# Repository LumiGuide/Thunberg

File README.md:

# THUNBERG CLIMATE CONTROL

An infrared controller for Fuji and Mitsubishi climate control units.
Visit thunberg.lumi.guide and select the room of the climate control unit you want to control under 'Room:'. It will load the last settings that were sent to this unit using the website. Set the preferred temperature, mode, strenth and extra options under 'toppings'. Click 'Send' to send a signal with these settings to the climate control unit, or click 'Turn off' to turn the unit off.
At the bottom of the page, you can click 'KILL ALL' to turn off all units in the rooms listed under 'Room:'.
Every day between 19:00 and 19:15, all units will be turned off automatically.

## Troubleshooting
- No response from the climate control unit
The Thunberg device works with an IR-LED, make sure there is nothing blocking the IR signal from the Thunberg device to the climate control unit. Make sure the IR-LED is pointing directly at the climate control unit.

If the LED on the back of the device is green, the device is connected to the internet. If this is not the case, unplug the device and plug it in again to reboot. It should automatically connect to the internet.
If the wifi name and/or password has changed, you need to change this in the menuconfig and flash the device. (Open the menuconfig by navigating to the Thunberg folder and using the command `idf.py menuconfig` in your terminal. ESP-IDF should be installed and running for this.)

- The webpage keeps loading
If there's no room selected, the page will remain on the loading screen. As soon as you select a room, it will load the last settings that were sent to the climate control unit in this room.
If there's a room selected, but the page keeps showing the loading screen, the website doesn't get a response from the device you selected. Check the internet connection of the device.

- The webpage is offline
The Master Device is offline. Unplug the device and plug it in again to reboot. It should automatically reconnect to the internet.

- It's still not working
Connect the device to your computer using the USB programmer and plug in the charger. With ESP-IDF running, type `idf.py -p USB-PORT monitor` in your terminal to see the data log.

# HOW TO BUILD

## Parts
- M5Stack M5Stamp Pico, ESP32-PICO-D4 (https://www.tinytronics.nl/shop/en/platforms-and-systems/m5stack/m5stamp/m5stamp/m5stack-m5stamp-pico-mate-esp32-pico-d4)
- IR LED, super-bright, 5mm, 940nm (https://www.adafruit.com/product/387)
- USB connector, USB4110-GF-A (https://www.digikey.nl/nl/products/detail/gct/USB4110-GF-A/10384547)
- Mosfet, N-channel, BSS214NWH6327XTSA1 (https://www.digikey.nl/nl/products/detail/infineon-technologies/BSS214NWH6327XTSA1/5959965https://www.digikey.nl/nl/products/detail/infineon-technologies/BSS214NWH6327XTSA1/5959965)
- Resistor, 100 Ohm, RC0603FR-07100RL (https://www.digikey.nl/nl/products/detail/yageo/RC0603FR-07100RL/726888)
- Resistor, 33.2 Ohm, CRCW060333R2FKEAHP (https://www.digikey.nl/nl/products/detail/vishay-dale/CRCW060333R2FKEAHP/2222239)
- PCB from file `thunberg.kicad_pcb` and `thunberg.kicad_sch`
- Case, 3D-printed from files `thunberg_case_body.stl` and `thunberg_case_lid.stl`
- M2 x 12mm screw, countersunk head (https://www.kingmicroschroeven.nl/bzk-inbus-verzonkenkopschroef-rvs-din-7991-m2x12.html)
- USB-C charger
- USB programmer FT232RL (https://www.otronic.nl/ft232rl-usb-ttl-serial-port-adapter-33v-5v.html)
- Breadboard and jumper wires to connect the USB programmer to the M5Stamp Pico
- ESP-IDF

## Soldering
Shorten the legs of the IR LED to about 4mm.
Solder the components on the PCB, using the `thunberg.kicad_sch` file for component names and `thunberg.kicad_pcb` for placement details.
Take the plastic casing of the M5Stamp Pico and solder the PCB on top of the M5Stamp Pico.

## Flash the device
Enter the WiFi settings in the menuconfig by navigating to the Thunberg folder and using the command `idf.py menuconfig` in your terminal (ESP-IDF should be installed and running for this) and go to `Thunberg Climate Control`.
Set the WiFi name under `WiFi SSID` and the corresponding password under `WiFi password`.

You'll need as much static IP-addresses as devices.
In `spiffs_data/index.html`, change the IP-addresses and corresponding room names if needed.

Connect the M5Stamp Pico to your laptop using the USB programmer and plug in the charger.
Flash one device using the host-settings. You can open the menuconfig by using the command `idf.py menuconfig` in your terminal (ESP-IDF should be installed and running for this). Go to `Thunberg Climate Control` > `Host website on this device` and select `Yes, host website`. This one will be the Master Device.
Select the right climate control brand under `Select airco brand`.
Save and close the menuconfig and flash the device by using the command `idf.py -p USB-PORT flash` in your terminal.

Flash the other devices without hosting a website on them. You can change this setting by opening the menuconfig by using the command `idf.py menuconfig` in your terminal and change the setting `Host website on this device` to `No, receive signals only` and make sure to select the right climate control brand.

Run the program on every single device while monitoring it using `idf.py -p USB-PORT monitor`.
In the terminal, you will be able to fetch its MAC-address in the line: `wifi:mode : sta (MAC)`.
In your router settings, link the MAC addresses of all devices to a static IP-address, and match these with the IP-addresses used in `spiffs_data/index.html`.
Optional: Create a convenient URL for the IP-address of the Master Device.

## How to use
Place the PCBs inside the cases and secure the lid with a screw. Mount the devices on the wall with the IR LED facing the climate control unit. The casing has some room for the IR LED to be adjusted. Power the devices with an USB-C charger.
When the LED on the back of the device turns green, it is connected to the internet.
Visit the IP-address of the Master Device. Here you can select the room of the climate control unit you want to control and the settings. 'Send' will send a signal to the selected climate control unit, ' Turn off' will turn this unit off. 'Kill all' will turn of all units in the rooms that are listed in the 'Room:' list on top of the page.
At the bottom of the page you see the date & time of the GET request and the last NTP synchronisation. This data can be used to see if the time and date are up to date. This is important for the next feature:
From monday to Friday, between 19:00 and 19:15, all units will be turned off automatically by sending a turn-off signal to every device.

## OTA
`/ota/new`:
To update the software, host a server with the compiled software in a `.bin`  file.
Place a POST request to the `/ota/new` URI of the IP-address of the device you want to update with the URL to the `.bin` file in the body. (You can use a program like Postman for this request.) The device will download the file and update the software. It will then restart and run the updated software. The old software is stored in another OTA slot in the Flash memory.

`/ota/commit`:
After running and testing the new software, you either have to commit this version or go back to the old version. Without committing, the version will remain in status ESP_OTA_IMG_PENDING_VERIFY and it will not be possible to update the software to a newer version. Also, in case of a restart, it will automatically change the status of this version to ESP_OTA_IMG_ABORTED and therefor it will not run.
To commit, place a POST request to the `/ota/commit` URI of the IP-address of the device you are updating.

`/ota/rollback`:
If you wish to go back to the old software version, it is possible to change the status of this version to ESP_OTA_IMG_ABORTED and restart the device. This version will not run due to its status and the old version will be selected with the reboot.
To roll back to the old version, place a POST request to the `/ota/rollback` URI of the device you were updating.

## TO DO
It's not possible to update the HTML-file using OTA updates. A software update should be written to provide this function.

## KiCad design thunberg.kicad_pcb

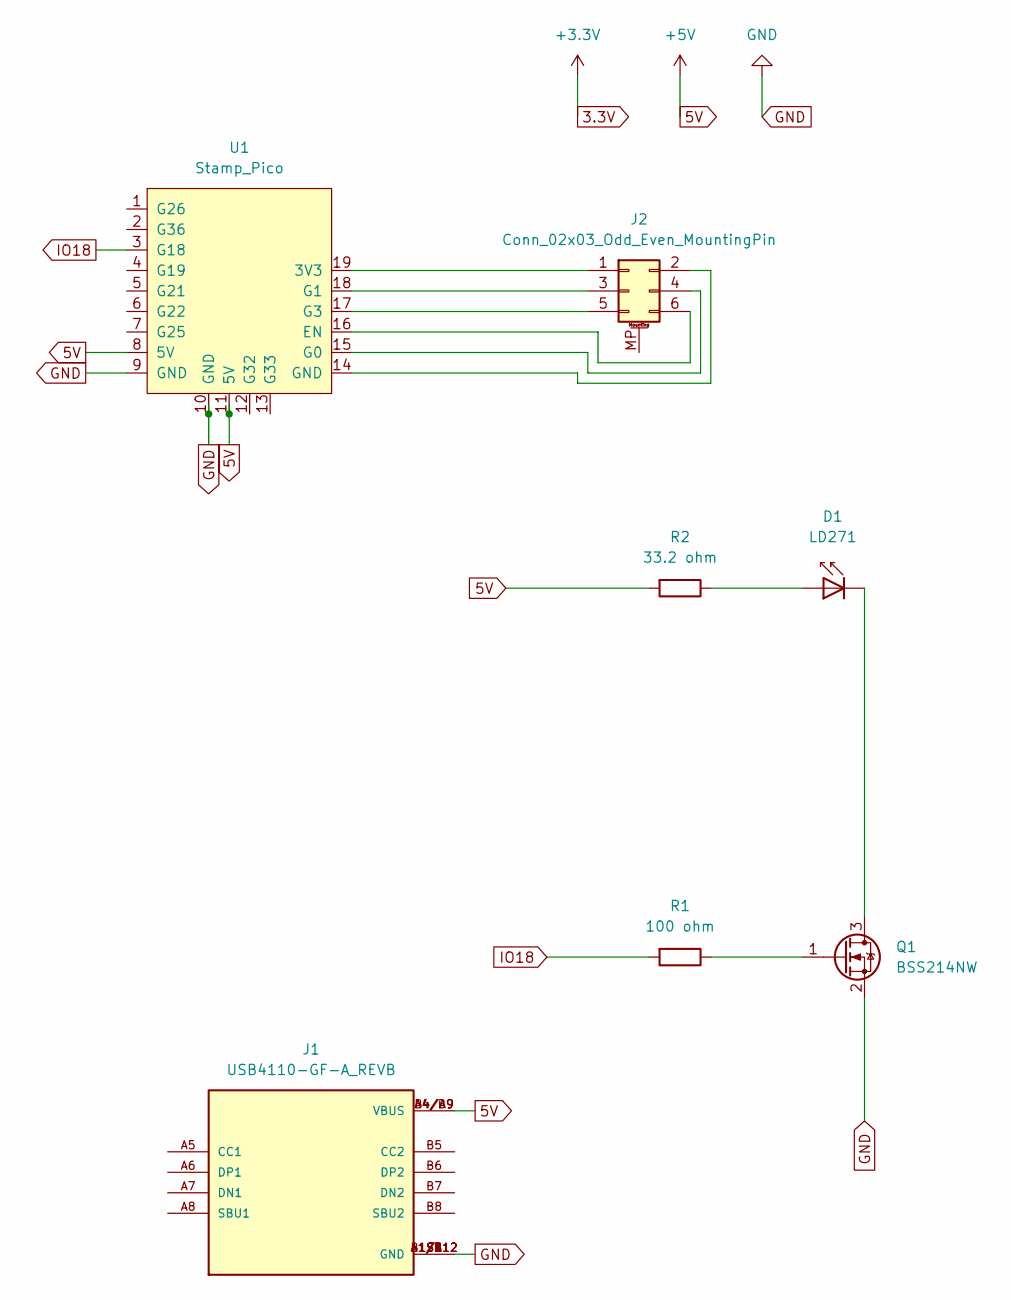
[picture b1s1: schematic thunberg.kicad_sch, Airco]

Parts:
D1: LD271; LED_D5.0mm_IRGrey
J1: USB4110-GF-A_REVB; GCT_USB4110-GF-A_REVB; PARTREV B
J2: Conn_02x03_Odd_Even_MountingPin; PinHeader_2x03_P1.00mm_Vertical
Q1: BSS214NW; SOT-323_SC-70
R1: 100 ohm; R_0603_1608Metric
R2: 33.2 ohm; R_0603_1608Metric
U1: Stamp_Pico; StampPico_template

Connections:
5V: J1.A4/B9 (VBUS), J1.B4/A9 (VBUS), R2.2, U1.8 (5V), U1.11 (5V)
GND: J1.A1/B12 (GND), J1.B1/A12 (GND), J1.S1 (GND), J1.S2 (GND), J1.S3 (GND), J1.S4 (GND), Q1.2 (S), U1.9 (GND), U1.10 (GND)
IO18: R1.2, U1.3 (G18)
unnamed: D1.1 (K), Q1.3 (D)
unnamed: D1.2 (A), R2.1
unnamed: J2.1, U1.19 (3V3)
unnamed: J2.2, U1.14 (GND)
unnamed: J2.3, U1.18 (G1)
unnamed: J2.4, U1.15 (G0)
unnamed: J2.5, U1.17 (G3)
unnamed: J2.6, U1.16 (EN)
unnamed: Q1.1 (G), R1.1

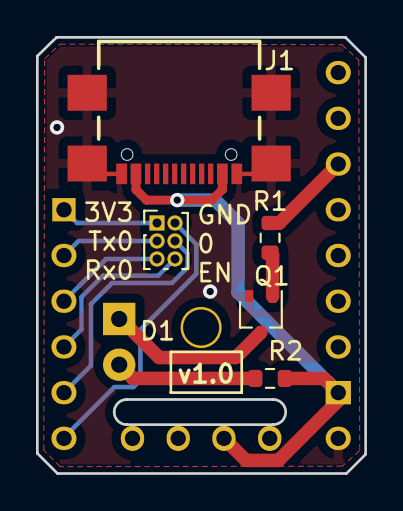
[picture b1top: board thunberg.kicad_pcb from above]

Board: 2 copper layers, 18.2 x 24.2 mm, 7 parts (1 on the bottom side), 12 nets.

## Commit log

2022-11-10 initial push of code
2022-11-15 merged header files, html page update
2022-11-23 website somewhat working
2022-11-23 website
2022-12-06 time sync, auto off
2022-12-07 semifinals: accuracy and exceptions mitsubishi airco
2022-12-08 final version
2022-12-15 turning on green LED when connected to WiFi
2022-12-15 website update
2022-12-28 case update
2023-01-04 CORS headers changed, webpage update
2023-01-05 OTA working but needs cleaning up
2023-06-13 WIP: infinite wifi reconnect
